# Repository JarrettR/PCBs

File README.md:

# PCBs
Not the environment-killing thing. Well, a little environment-killing.

# What is this?
Just doodles. In hardware. Any project that is documented here that turns serious will get spun off into its own repo.

Most of the things that make it to a boardhouse will end up being described at http://www.jrainimo.com in some form.

I will attempt to include a short readme with an overview of the project in each folder. Sometimes, the purpose of a design is not obvious without an explanation. Many of them, however, have no explanation.

The folders are numbered chronologically, approximately. This means that higher numbers will be more recent, and therefore more interesting, generally.

# What's good?

### Time

### Shallow

### ColourTest

### Raspberry-Power

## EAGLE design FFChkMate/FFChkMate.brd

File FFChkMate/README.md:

# What is this?
A breakout board for 0.14mm pitch Flexible Flat Cable (FFC) connectors.

 Most of the little flex cables you see in consumer electronics use these connectors. They are a pain in the dick to troubleshoot, repair, or reverse engineer.

So this is a breakout board, with a couple twists.

Even-numbered FFC connectors are pretty straightforward. The pins on the footprint are directly across from each other, like any standard DIP or rectangular SMD semiconductor.
 
Odd-numbered connectors, however, are staggered. Kinda like a SOT-3 package, extended out to however many pins are involved.
 
 .
 
This board reconciles those differences. There are three rows of solder pads. The middle row starts at pin 1, and counts up to 3, 5, etc. On either side of that row, however, there are pads 2, 4, 6, etc.

On one side the pads are staggered. On the other side, the pads are in-line. So with this one board, you have a choice of using an odd- or even-numbered connector. Awesome.
 
.
 
Additionally, it has 51 pins, so it'll work for any pincount up to and including that.
 
.
 
One more feature:
With a little bit of critical thought, you can set up two boards with the appropriate connector, buy an extra flex cable, and then solder both boards together (with header pins).
That will pass the signal from one portion of your device to the proper endpoint, but you'll have a debug / logic analysis area in the middle.

# More info
http://jrainimo.com/build/?p=482

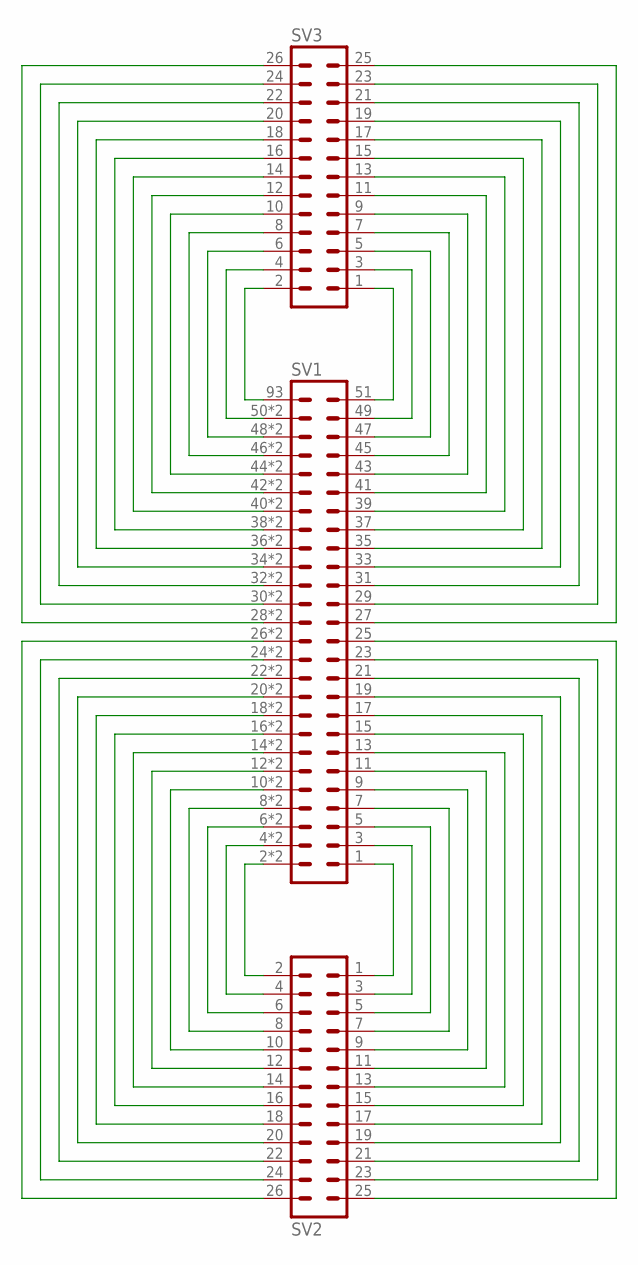
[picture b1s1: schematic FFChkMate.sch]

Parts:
SV1: 03MM
SV2, SV3: MA13-2

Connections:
unnamed: SV1.1, SV2.1
unnamed: SV1.3, SV2.3
unnamed: SV1.5, SV2.5
unnamed: SV1.7, SV2.7
unnamed: SV1.9, SV2.9
unnamed: SV1.11, SV2.11
unnamed: SV1.13, SV2.13
unnamed: SV1.15, SV2.15
unnamed: SV1.17, SV2.17
unnamed: SV1.19, SV2.19
unnamed: SV1.21, SV2.21
unnamed: SV1.23, SV2.23
unnamed: SV1.25, SV2.25
unnamed: SV1.2, SV1.68 (2), SV2.2
unnamed: SV1.4, SV1.69 (4), SV2.4
unnamed: SV1.6, SV1.70 (6), SV2.6
unnamed: SV1.8, SV1.71 (8), SV2.8
unnamed: SV1.10, SV1.72 (10), SV2.10
unnamed: SV1.12, SV1.73 (12), SV2.12
unnamed: SV1.14, SV1.74 (14), SV2.14
unnamed: SV1.16, SV1.75 (16), SV2.16
unnamed: SV1.18, SV1.76 (18), SV2.18
unnamed: SV1.20, SV1.77 (20), SV2.20
unnamed: SV1.22, SV1.78 (22), SV2.22
unnamed: SV1.24, SV1.79 (24), SV2.24
unnamed: SV1.26, SV1.80 (26), SV2.26
unnamed: SV1.51, SV3.1
unnamed: SV1.49, SV3.3
unnamed: SV1.47, SV3.5
unnamed: SV1.45, SV3.7
unnamed: SV1.43, SV3.9
unnamed: SV1.41, SV3.11
unnamed: SV1.39, SV3.13
unnamed: SV1.37, SV3.15
unnamed: SV1.35, SV3.17
unnamed: SV1.33, SV3.19
unnamed: SV1.31, SV3.21
unnamed: SV1.29, SV3.23
unnamed: SV1.27, SV3.25
unnamed: SV1.93 (52), SV3.2
unnamed: SV1.50, SV1.92 (50), SV3.4
unnamed: SV1.48, SV1.91 (48), SV3.6
unnamed: SV1.46, SV1.90 (46), SV3.8
unnamed: SV1.44, SV1.89 (44), SV3.10
unnamed: SV1.42, SV1.88 (42), SV3.12
unnamed: SV1.40, SV1.87 (40), SV3.14
unnamed: SV1.38, SV1.86 (38), SV3.16
unnamed: SV1.36, SV1.85 (36), SV3.18
unnamed: SV1.34, SV1.84 (34), SV3.20
unnamed: SV1.32, SV1.83 (32), SV3.22
unnamed: SV1.30, SV1.82 (30), SV3.24
unnamed: SV1.28, SV1.81 (28), SV3.26

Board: 2 copper layers, 3 parts (0 on the bottom side), 52 nets, no tracks yet.

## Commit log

2015-05-04 Initial with many of my projects from the past six months
2015-05-04 Added library
2015-05-14 Added FFC breakout
2015-05-14 Typo
2015-06-29 Old commit
2015-06-29 Added automagic supplier links for purchasing
2015-06-30 Added gerbers
2015-07-03 Added large nut logo, creator info to silk
2015-07-09 Started catch-all panelisation project, added simple motor driver
2015-07-09 Rewrote clearerer
2015-07-10 All panels moved and completed
2015-07-30 Added non-proprietary images
2015-09-04 PWM lookup, ATX PS, and some tweaks
2015-10-26 Cleanup, improved documentation
2015-10-26 Added LED and started USP
2016-01-25 UPS PCB done almost
2016-01-26 Fixed up USB, added logo
2016-01-27 UPS outputs and images
2016-01-27 Improved UPS docs
2016-02-12 Added USB thing
2016-02-15 Added panel for UPS and USB PIC
2016-03-08 USB updates, test project 555 and PaneLED
2016-03-23 Moved USB Thing to its own repo, added PaneLED + outputs, toyed around with 555
2016-03-31 PaneLED add images
2016-04-07 Started testing PicKit (finally!)
2016-05-10 Done panelising UPS, I think
2016-05-10 Oops, missed corner radii in GM1
2016-05-10 Removed stray mechanical layer line
2016-10-18 Added RGBToken
2016-10-19 Added my favourite libraries
2016-10-19 Added panel of RGB tokens
2016-10-19 Added RGB Token docs
2017-02-10 Updated RGBToken docs
2017-02-10 Ridiculous colour test is ridiculous
2017-02-27 Added DFBR030U3LP
2017-02-27 Updated libraries
2017-03-22 Added huge Altium library
2017-06-01 Documentation improvements
2017-10-04 Motor controller
2017-10-04 Big organisational reshuffle
2017-10-05 Added RingLED
2017-10-05 Added RingLED readme
2017-10-25 Doc updates for RingLED
2018-01-18 Folders sorted using leading zeros
2018-01-18 Added SMPS projects
2018-05-04 Added Shallow
2018-05-04 Removed leading slashes in images
2018-05-18 Added Shallow PCB image
2018-06-11 Uploaded Shallow assembled image
2019-02-12 Pushing old panels, new designs
2019-10-25 Initial Time project
2019-11-08 OD to 38mm, added more spirals
2019-11-08 Added outline tabs
2019-11-14 Added all vias
2019-11-15 Expand to 4-layer and add bottom spiral to shape
2019-11-22 Added half bridge IC
2019-12-07 12 oclock routed
2019-12-07 Improved MOSFET footprint
2019-12-08 Routed MOSFET
2019-12-10 12 oclock fully routed
2019-12-11 Cleanup tweaks
2019-12-13 Routes done for all outer coils
2019-12-13 Teardrop solderpads placed
2019-12-13 Outer FETs placed
2019-12-14 Solderpads and ground planes
2019-12-16 Solderpad and via pos adjustments
2019-12-18 Inner traces and design features
2019-12-23 Inner components complete
2019-12-23 Manufacturing tweaks
2019-12-23 Added roman numerals
2020-04-04 Globall and swapping around readme
2020-04-05 Add Time
